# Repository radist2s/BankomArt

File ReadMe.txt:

BankomArt
  Project
  ----------------------------------
  Developed with embedXcode

  Project BankomArt
  Created by Александр Баталов on 24.12.14
  Copyright © 2014 Александр Баталов
  License <#license#>

  References
  ----------------------------------

  embedXcode
  embedXcode+
  ----------------------------------
  Embedded Computing on Xcode
  Copyright © Rei VILO, 2010-2014
  All rights reserved
  http://embedXcode.weebly.com

diecimila
atmega328
diecimila.menu.cpu.atmega328

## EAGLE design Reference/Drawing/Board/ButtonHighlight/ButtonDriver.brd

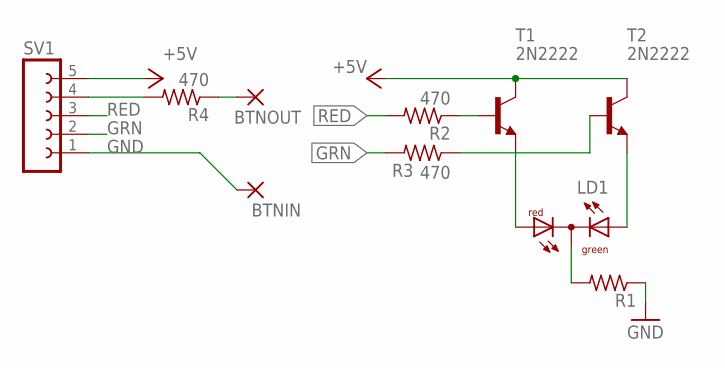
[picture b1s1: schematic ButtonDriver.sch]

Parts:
BTNIN: 2,54/0,9
BTNOUT: 2,54/0,9
LD1: DUOLED-RG-C; DUOLED-C-5MM
R1: R-US_0207/10; 0207/10
R2, R3, R4: 470; 0207/10
SV1: FE05-1
T1, T2: 2N2222; TO92-EBC-OVAL

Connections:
+5V: SV1.5, T1.C, T2.C
GND: BTNIN.1, R1.1, SV1.1
GRN: R3.2, SV1.2
unnamed: LD1.AR, T1.E
unnamed: LD1.C, R1.2
unnamed: LD1.AX (AG), T2.E
unnamed: R3.1, T2.B
unnamed: R2.1, T1.B
unnamed: R4.2, SV1.4
unnamed: BTNOUT.1, R4.1
RED: R2.2, SV1.3

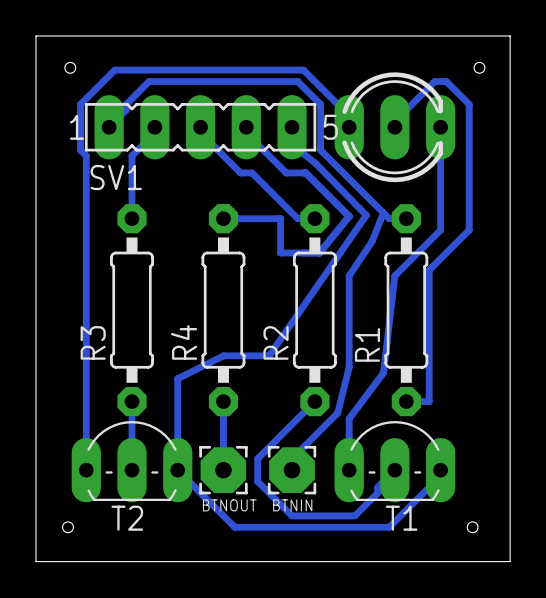
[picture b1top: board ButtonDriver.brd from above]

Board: 2 copper layers, 26.3 x 29.2 mm, 10 parts (0 on the bottom side), 11 nets.

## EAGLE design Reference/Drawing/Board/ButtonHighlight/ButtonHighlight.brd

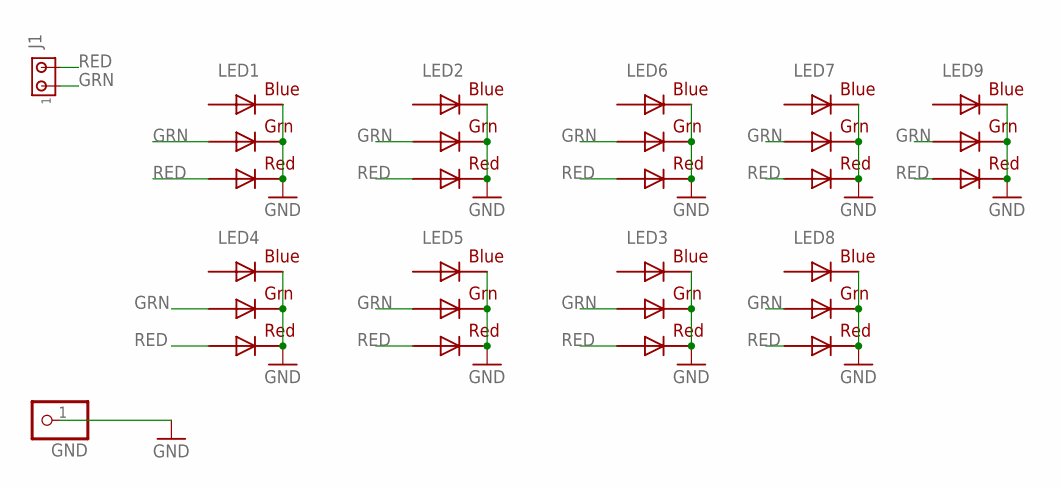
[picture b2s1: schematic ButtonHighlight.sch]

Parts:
GND: PINHD-1X1; 1X01
J1: MTA02-100; 10X02MTA
LED1, LED2, LED3, LED4, LED5, LED6, LED7, LED8, LED9: RGBLED5050

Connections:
GND: GND.1, LED1.4 (BLUE_C), LED1.5 (RED_C), LED1.6 (GREEN_C), LED2.4 (BLUE_C), LED2.5 (RED_C), LED2.6 (GREEN_C), LED3.4 (BLUE_C), LED3.5 (RED_C), LED3.6 (GREEN_C), LED4.4 (BLUE_C), LED4.5 (RED_C), LED4.6 (GREEN_C), LED5.4 (BLUE_C), LED5.5 (RED_C), LED5.6 (GREEN_C), LED6.4 (BLUE_C), LED6.5 (RED_C), LED6.6 (GREEN_C), LED7.4 (BLUE_C), LED7.5 (RED_C), LED7.6 (GREEN_C), LED8.4 (BLUE_C), LED8.5 (RED_C), LED8.6 (GREEN_C), LED9.4 (BLUE_C), LED9.5 (RED_C), LED9.6 (GREEN_C)
GRN: J1.1, LED1.1 (GREEN_A), LED2.1 (GREEN_A), LED3.1 (GREEN_A), LED4.1 (GREEN_A), LED5.1 (GREEN_A), LED6.1 (GREEN_A), LED7.1 (GREEN_A), LED8.1 (GREEN_A), LED9.1 (GREEN_A)
RED: J1.2, LED1.2 (RED_A), LED2.2 (RED_A), LED3.2 (RED_A), LED4.2 (RED_A), LED5.2 (RED_A), LED6.2 (RED_A), LED7.2 (RED_A), LED8.2 (RED_A), LED9.2 (RED_A)

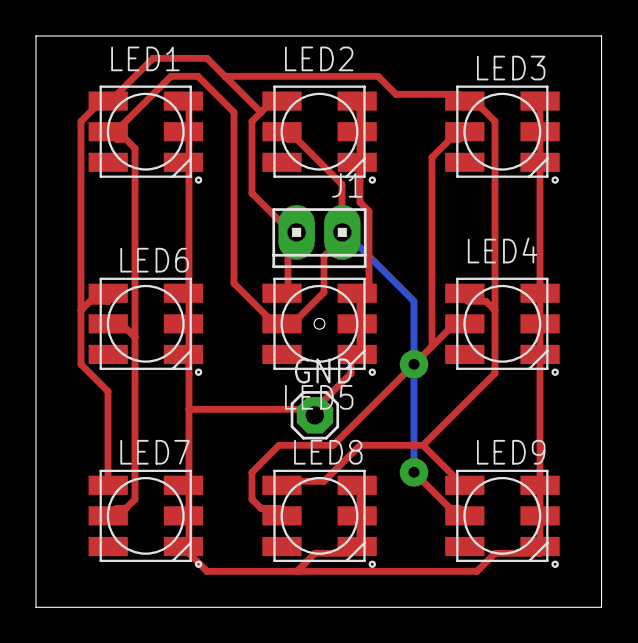
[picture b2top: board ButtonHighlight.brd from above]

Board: 2 copper layers, 31.4 x 31.7 mm, 11 parts (0 on the bottom side), 3 nets.

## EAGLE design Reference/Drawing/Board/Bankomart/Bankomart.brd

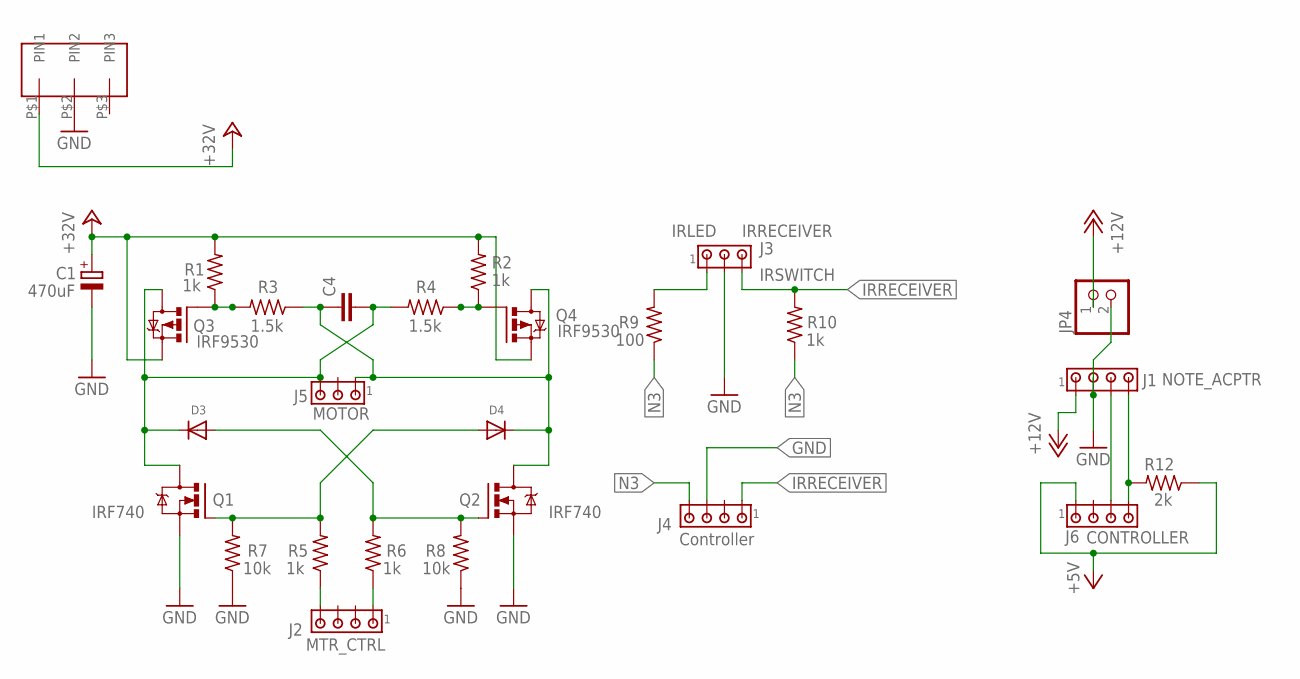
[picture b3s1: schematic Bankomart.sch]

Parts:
C1: 470uF; E7,5-18
C4: C-EU050-025X075; C050-025X075
D3, D4: DIODEDO-1N4148; DO-1N4148
J1: NOTE_ACPTR; 10X04MTA
J2: MTR_CTRL; 10X04MTA
J3: IRSWITCH; 10X03MTA
J4: Controller; 10X04MTA
J5: MOTOR; 10X03MTA
J6: CONTROLLER; 10X04MTA
JP4: PINHD-1X2; 1X02
Q1, Q2: IRF740; TO220BV
Q3, Q4: IRF9530; TO220BV
R1, R2, R5, R6, R10: 1k; 0207/10
R3, R4: 1.5k; 0207/10
R7, R8: 10k; 0207/10
R9: 100; 0207/10
R12: 2k; 0207/10
U$1: CUSTOM-PIN-3

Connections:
+5V: J6.1, R12.1
+12V: J1.1, JP4.1
+24V: C1.+, Q3.S, Q4.S, R1.2, R2.2, U$1.P$1 (PIN1)
GND: C1.-, J1.2, J3.2, J4.3, JP4.2, Q1.S, Q2.S, R7.1, R8.1, U$1.P$2 (PIN2)
IRLED: J3.1, R9.2
IRRECEIVER: J3.3, J4.1, R10.2
MOTOR_B: J2.1, R6.1
MOTOR_F: J2.4, R5.1
N3: J4.4, R9.1, R10.1
unnamed: Q3.G, R1.1, R3.2
unnamed: C4.1, D4.C, J5.1, Q2.D, Q4.D, R3.1
unnamed: C4.2, D3.C, J5.3, Q1.D, Q3.D, R4.2
unnamed: Q4.G, R2.1, R4.1
unnamed: D3.A, Q2.G, R6.2, R8.2
unnamed: D4.A, Q1.G, R5.2, R7.2
unnamed: J1.3, J6.3
unnamed: J1.4, J6.4, R12.2

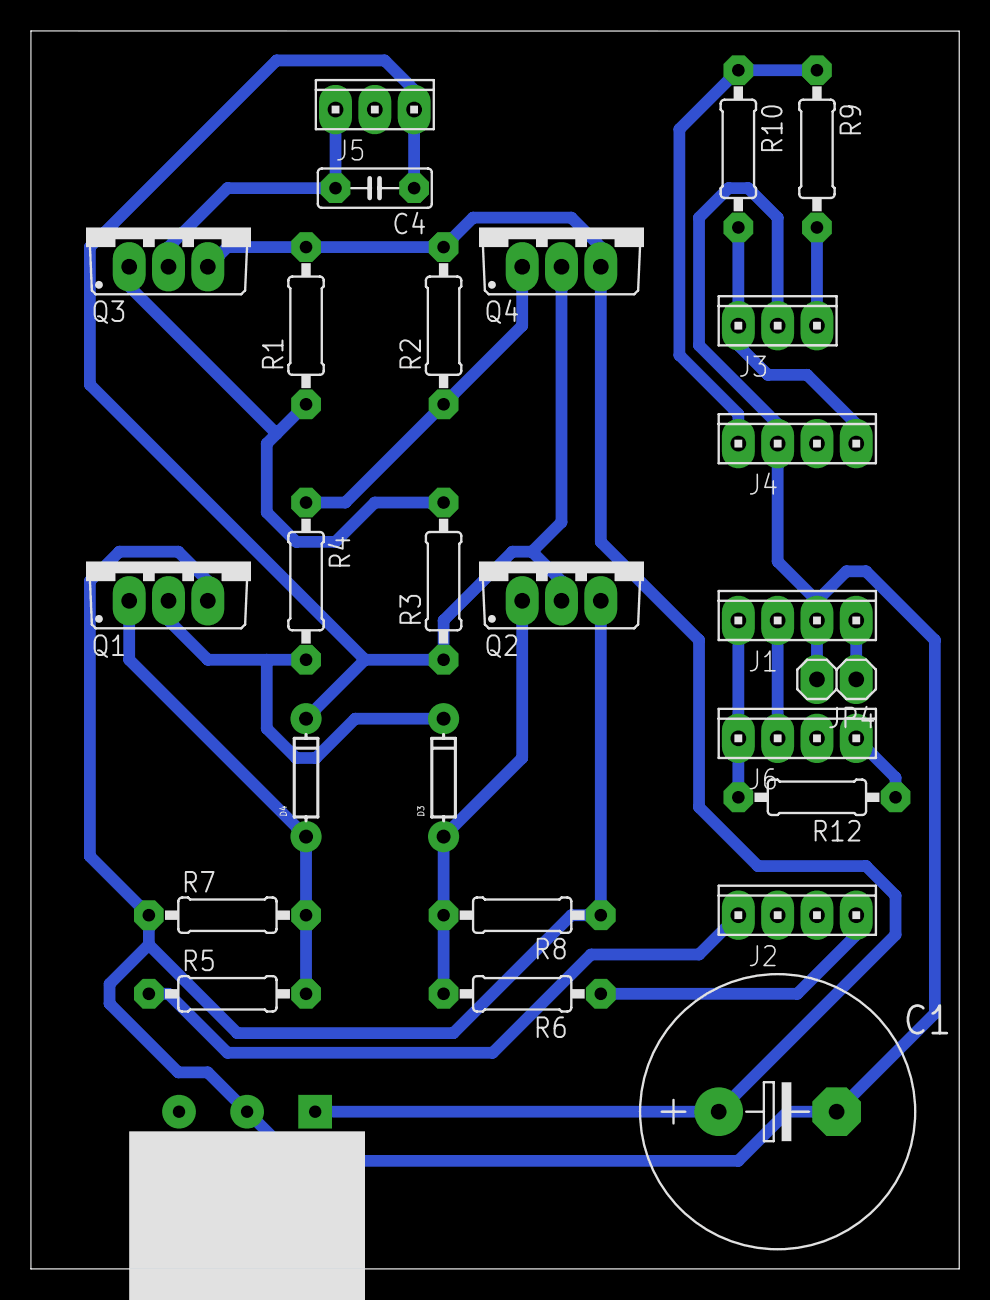
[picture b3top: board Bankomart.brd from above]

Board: 2 copper layers, 60.0 x 80.0 mm, 27 parts (0 on the bottom side), 17 nets.

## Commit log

2015-05-03 Release 1.0
2015-05-03 Board circuitry added (Eagle Project)
